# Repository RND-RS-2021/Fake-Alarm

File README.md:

Fake Alarm design for PT. Radiator Springs Indonesia 

Contributor: 
*Nur Imam P, Husain Asyari, Maruf Wahyu P*

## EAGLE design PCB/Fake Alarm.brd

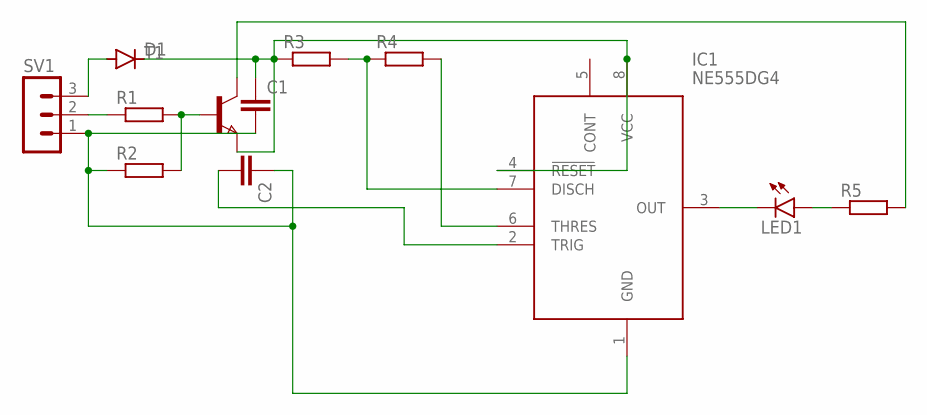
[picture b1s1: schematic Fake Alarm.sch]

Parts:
C1, C2: C-EUC0805; C0805
D1: DIODE-DO-214AC; DO-214AC
IC1: NE555DG4; SOIC127P600X175-8N
LED1: LEDKA-3528ASYC; KA-3528ASYC
R1, R2, R3, R4, R5: R-EU_M0805; M0805
SV1: MA03-1
T1: NPNSOT23; SOT-23

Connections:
unnamed: D1.A, SV1.3
unnamed: R1.1, SV1.2
unnamed: C1.2, C2.1, IC1.1 (GND), R2.1, SV1.1
unnamed: C1.1, D1.C, IC1.4 (!RESET), IC1.8 (VCC), R3.1, T1.2 (E)
unnamed: R1.2, R2.2, T1.3 (B)
unnamed: IC1.7 (DISCH), R3.2, R4.1
unnamed: C2.2, IC1.2 (TRIG)
unnamed: IC1.3 (OUT), LED1.C
unnamed: LED1.A, R5.1
unnamed: R5.2, T1.1 (C)
unnamed: IC1.6 (THRES), R4.2

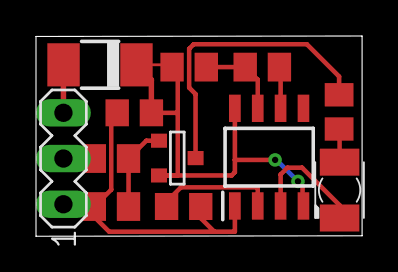
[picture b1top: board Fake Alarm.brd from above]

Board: 2 copper layers, 18.1 x 11.1 mm, 12 parts (0 on the bottom side), 11 nets.

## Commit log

2021-08-16 Submit
2021-08-21 New Design Fake Alarm Schematic and Layout
